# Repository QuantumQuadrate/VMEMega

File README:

VMEMega is a modified ardunino mega board designed to fit into the VME system designed for Saffman lab.
It has 3 communication interfaces (USB/Serial, Ethernet, I2C over backplane) and is designed to host normal mega compatible arduino shields.

Matthew Ebert
Atom Trainers (Walker Lab) and Saffman Lab

Licenced uner the Arduino Creative Commons Share-Alike licence.

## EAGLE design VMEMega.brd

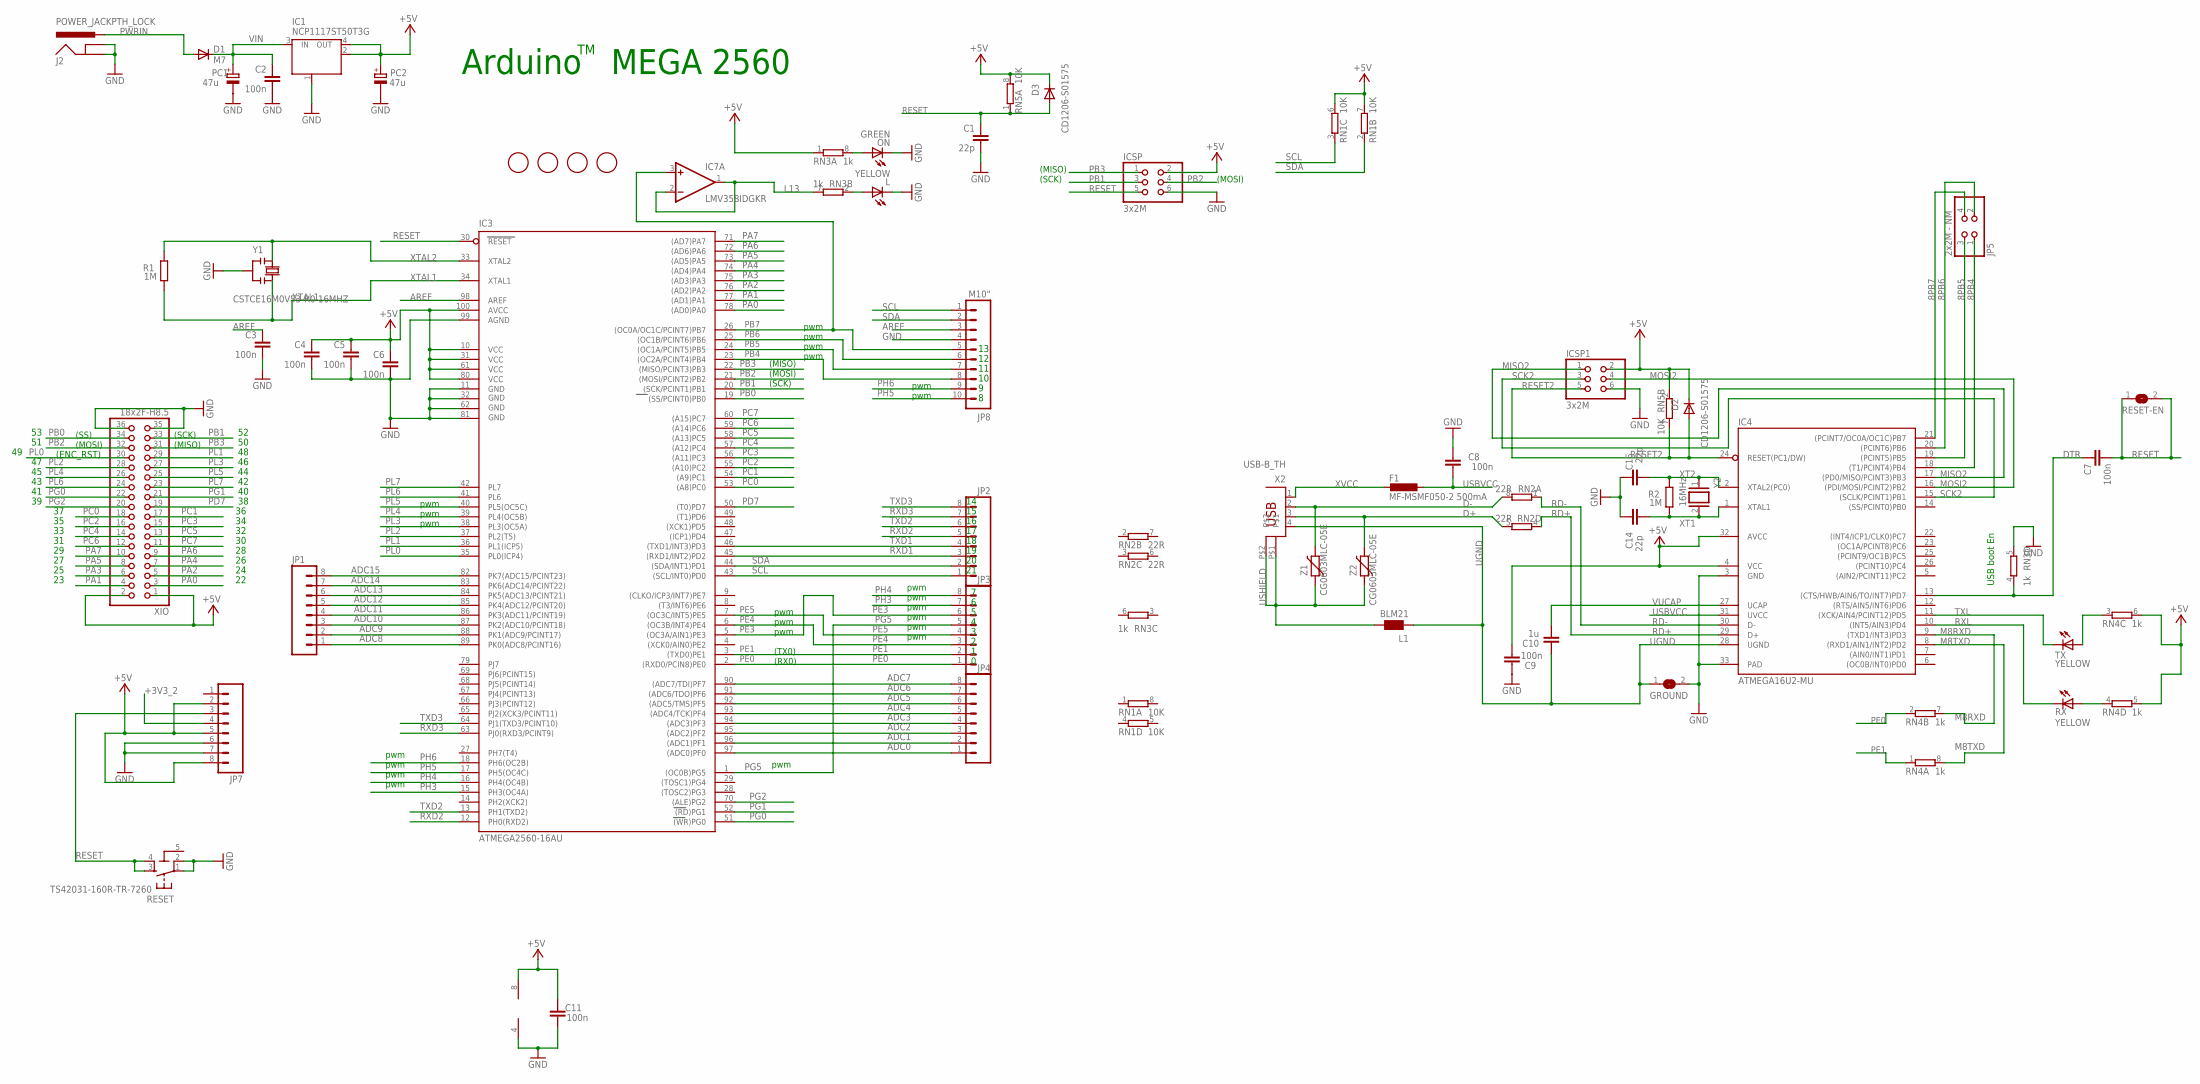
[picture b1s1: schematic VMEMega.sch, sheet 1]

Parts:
C1, C14, C15: 22p; C0603-ROUND
C2, C3, C4, C5, C6, C7, C8, C9, C11: 100n; C0603-ROUND
C10: 1u; C0603-ROUND
D1: M7; SMB
D2, D3: CD1206-S01575; MINIMELF
F1: MF-MSMF050-2 500mA; L1812
FD1, FD2, FD3, FD4: FIDUCIALMOUNT; FIDUCIA-MOUNT
GROUND: SJ
IC1: NCP1117ST50T3G; SOT223
IC3: ATMEGA2560-16AU; TQFP100
IC4: ATMEGA16U2-MU; MLF32
IC7: LMV358IDGKR; MSOP08
ICSP, ICSP1: 3x2M; 2X03
J2: POWER_JACKPTH_LOCK; POWER_JACK_PTH_LOCK
JP1, JP2, JP3, JP4, JP7: M081X08; 1X08
JP5: 2x2M - NM; 2X02
JP8: M10"; 1X10
L: YELLOW; CHIP-LED0805
L1: BLM21; 0805
ON: GREEN; CHIP-LED0805
PC1, PC2: 47u; PANASONIC_D
R1, R2: 1M; R0603-ROUND
RESET: TS42031-160R-TR-7260; TS42
RESET-EN: SJ
RN1, RN5: 10K; CAT16
RN2: 22R; CAY16
RN3, RN4: 1k; CAY16
RX: YELLOW; CHIP-LED0805
TX: YELLOW; CHIP-LED0805
X2: USB-B_TH; PN61729
XIO: 18x2F-H8.5; 2X18
Y1: CSTCE16M0V53-R0 16MHZ; RESONATOR
Y2: 16MHz; QS
Z1, Z2: CG0603MLC-05E; CT/CN0603

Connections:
5-GND: RESET.5 (5-GND)
8PB4: IC4.18 ((T1/PCINT4)PB4), JP5.1
8PB5: IC4.19 ((PCINT5)PB5), JP5.3
8PB6: IC4.20 ((PCINT6)PB6), JP5.2
8PB7: IC4.21 ((PCINT7/OC0A/OC1C)PB7), JP5.4
+3V3_2: JP7.4; also elsewhere on the board
+5V: C4.1, C5.1, C6.1, C9.1, C11.2, D2.C, D3.C, IC1.2 (OUT), IC1.4 (OUT), IC3.10 (VCC), IC3.31 (VCC1), IC3.61 (VCC2), IC3.80 (VCC3), IC3.100 (AVCC), IC4.4 (VCC), IC4.32 (AVCC), IC7.8 (V+), ICSP.2, ICSP1.2, JP7.2, JP7.5, JP7.8, PC2.+, RN1.6 (2), RN1.7 (2), RN3.1, RN4.5 (2), RN4.6 (2), RN5.2 (1), RN5.8 (2), XIO.1, XIO.2; also elsewhere on the board
ADC0: IC3.97 ((ADC0)PF0), JP4.1
ADC1: IC3.96 ((ADC1)PF1), JP4.2
ADC2: IC3.95 ((ADC2)PF2), JP4.3
ADC3: IC3.94 ((ADC3)PF3), JP4.4
ADC4: IC3.93 ((ADC4/TCK)PF4), JP4.5
ADC5: IC3.92 ((ADC5/TMS)PF5), JP4.6
ADC6: IC3.91 ((ADC6/TDO)PF6), JP4.7
ADC7: IC3.90 ((ADC7/TDI)PF7), JP4.8
ADC8: IC3.89 (PK0(ADC8/PCINT16)), JP1.1
ADC9: IC3.88 (PK1(ADC9/PCINT17)), JP1.2
ADC10: IC3.87 (PK2(ADC10/PCINT18)), JP1.3
ADC11: IC3.86 (PK3(ADC11/PCINT19)), JP1.4
ADC12: IC3.85 (PK4(ADC12/PCINT20)), JP1.5
ADC13: IC3.84 (PK5(ADC13/PCINT21)), JP1.6
ADC14: IC3.83 (PK6(ADC14/PCINT22)), JP1.7
ADC15: IC3.82 (PK7(ADC15/PCINT23)), JP1.8
AREF: C3.1, IC3.98 (AREF), JP8.3; also elsewhere on the board
D+: RN2.5 (2), X2.3, Z2.2
D-: RN2.8 (2), X2.2, Z1.2
DTR: C7.1, IC4.13 ((CTS/HWB/AIN6/TO/INT7)PD7), RN3.4 (1)
GND: C1.2, C2.2, C3.2, C4.2, C5.2, C6.2, C8.2, C9.2, C11.1, C14.2, C15.2, GROUND.2, IC1.1 (GND/ADJ), IC3.11 (GND), IC3.32 (GND1), IC3.62 (GND2), IC3.81 (GND3), IC3.99 (AGND), IC4.3 (GND), IC4.33 (PAD), IC7.4 (V-), ICSP.6, ICSP1.6, J2.GND, J2.GNDBREAK, JP7.6, JP7.7, JP8.4, L.C, ON.C, PC1.-, PC2.-, RESET.1, RESET.2, RN3.5 (2), XIO.35, XIO.36, Y1.2; also elsewhere on the board
L13: IC7.1 (OUT), IC7.2 (-IN), RN3.7 (2)
M8RXD: IC4.9 ((TXD1/INT3)PD3), RN4.7 (2)
M8TXD: IC4.8 ((RXD1/AIN1/INT2)PD2), RN4.8 (2)
MISO2: IC4.17 ((PD0/MISO/PCINT3)PB3), ICSP1.1
MOSI2: IC4.16 ((PDI/MOSI/PCINT2)PB2), ICSP1.4
unnamed: L.A, RN3.2 (1)
unnamed: ON.A, RN3.8 (2)
unnamed: RN4.4 (1), RX.A
unnamed: RN4.3 (1), TX.A
PA0: IC3.78 ((AD0)PA0), XIO.3
PA1: IC3.77 ((AD1)PA1), XIO.4
PA2: IC3.76 ((AD2)PA2), XIO.5
PA3: IC3.75 ((AD3)PA3), XIO.6
PA4: IC3.74 ((AD4)PA4), XIO.7
PA5: IC3.73 ((AD5)PA5), XIO.8
PA6: IC3.72 ((AD6)PA6), XIO.9
PA7: IC3.71 ((AD7)PA7), XIO.10
PB0: IC3.19 ((SS/PCINT0)PB0), XIO.34; also elsewhere on the board
PB1: IC3.20 ((SCK/PCINT1)PB1), ICSP.3, XIO.33; also elsewhere on the board
PB2: IC3.21 ((MOSI/PCINT2)PB2), ICSP.4, XIO.32; also elsewhere on the board
PB3: IC3.22 ((MISO/PCINT3)PB3), ICSP.1, XIO.31; also elsewhere on the board
PB4: IC3.23 ((OC2A/PCINT4)PB4), JP8.8
PB5: IC3.24 ((OC1A/PCINT5)PB5), JP8.7
PB6: IC3.25 ((OC1B/PCINT6)PB6), JP8.6
PB7: IC3.26 ((OC0A/OC1C/PCINT7)PB7), IC7.3 (+IN), JP8.5
PC0: IC3.53 ((A8)PC0), XIO.18
PC1: IC3.54 ((A9)PC1), XIO.17
PC2: IC3.55 ((A10)PC2), XIO.16
PC3: IC3.56 ((A11)PC3), XIO.15
PC4: IC3.57 ((A12)PC4), XIO.14
PC5: IC3.58 ((A13)PC5), XIO.13
PC6: IC3.59 ((A14)PC6), XIO.12
PC7: IC3.60 ((A15)PC7), XIO.11
PD7: IC3.50 ((T0)PD7), XIO.19
PE0: IC3.2 ((RXD0/PCIN8)PE0), JP3.1, RN4.2 (1)
PE1: IC3.3 ((TXD0)PE1), JP3.2, RN4.1
PE3: IC3.5 ((OC3A/AIN1)PE3), JP3.6
PE4: IC3.6 ((OC3B/INT4)PE4), JP3.3
PE5: IC3.7 ((OC3C/INT5)PE5), JP3.4
PG0: IC3.51 ((WR)PG0), XIO.22
PG1: IC3.52 ((RD)PG1), XIO.21
PG2: IC3.70 ((ALE)PG2), XIO.20
PG5: IC3.1 ((OC0B)PG5), JP3.5
PH3: IC3.15 (PH3(OC4A)), JP3.7
PH4: IC3.16 (PH4(OC4B)), JP3.8
PH5: IC3.17 (PH5(OC4C)), JP8.10
PH6: IC3.18 (PH6(OC2B)), JP8.9
PL0: IC3.35 (PL0(ICP4)), XIO.30; also elsewhere on the board
PL1: IC3.36 (PL1(ICP5)), XIO.29
PL2: IC3.37 (PL2(T5)), XIO.28
PL3: IC3.38 (PL3(OC5A)), XIO.27
PL4: IC3.39 (PL4(OC5B)), XIO.26
PL5: IC3.40 (PL5(OC5C)), XIO.25
PL6: IC3.41 (PL6), XIO.24
PL7: IC3.42 (PL7), XIO.23
PWRIN: D1.A, J2.PWR
RD+: IC4.29 (D+), RN2.4 (1)
RD-: IC4.30 (D-), RN2.1
RESET: C1.1, C7.2, D3.A, IC3.30 (RESET), ICSP.5, JP7.3, RESET.3, RESET.4, RESET-EN.1, RESET-EN.2, RN5.1
RESET2: D2.A, IC4.24 (RESET(PC1/DW)), ICSP1.5, RN5.7 (2)
RXD1: IC3.45 ((RXD1/INT2)PD2), JP2.3
RXD2: IC3.12 (PH0(RXD2)), JP2.5
RXD3: IC3.63 (PJ0(RXD3/PCINT9)), JP2.7
RXL: IC4.10 ((INT5/AIN3)PD4), RX.C
SCK2: IC4.15 ((SCLK/PCINT1)PB1), ICSP1.3
SCL: IC3.43 ((SCL/INT0)PD0), JP2.1, JP8.1, RN1.3 (1); also elsewhere on the board
SDA: IC3.44 ((SDA/INT1)PD1), JP2.2, JP8.2, RN1.2 (1); also elsewhere on the board
TXD1: IC3.46 ((TXD1/INT3)PD3), JP2.4
TXD2: IC3.13 (PH1(TXD2)), JP2.6
TXD3: IC3.64 (PJ1(TXD3/PCINT10)), JP2.8
TXL: IC4.11 ((XCK/AIN4/PCINT12)PD5), TX.C
UGND: C10.2, GROUND.1, IC4.28 (UGND), L1.1, X2.4
USBVCC: C8.1, F1.1, IC4.31 (UVCC)
USHIELD: L1.2, X2.P$1, X2.P$2, Z1.1, Z2.1
VIN: C2.1, D1.C, IC1.3 (IN), PC1.+
VUCAP: C10.1, IC4.27 (UCAP)
XT1: C14.1, IC4.1 (XTAL1), R2.1, Y2.2
XT2: C15.1, IC4.2 (XTAL2(PC0)), R2.2, Y2.1
XTAL1: IC3.34 (XTAL1), R1.1, Y1.3
XTAL2: IC3.33 (XTAL2), R1.2, Y1.1
XVCC: F1.2, X2.1

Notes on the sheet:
Arduino MEGA 2560
(SCK)
(MISO)
(MOSI)
pwm
(TX0)
(RX0)
(SS)
USB boot En
(ENC_RST)

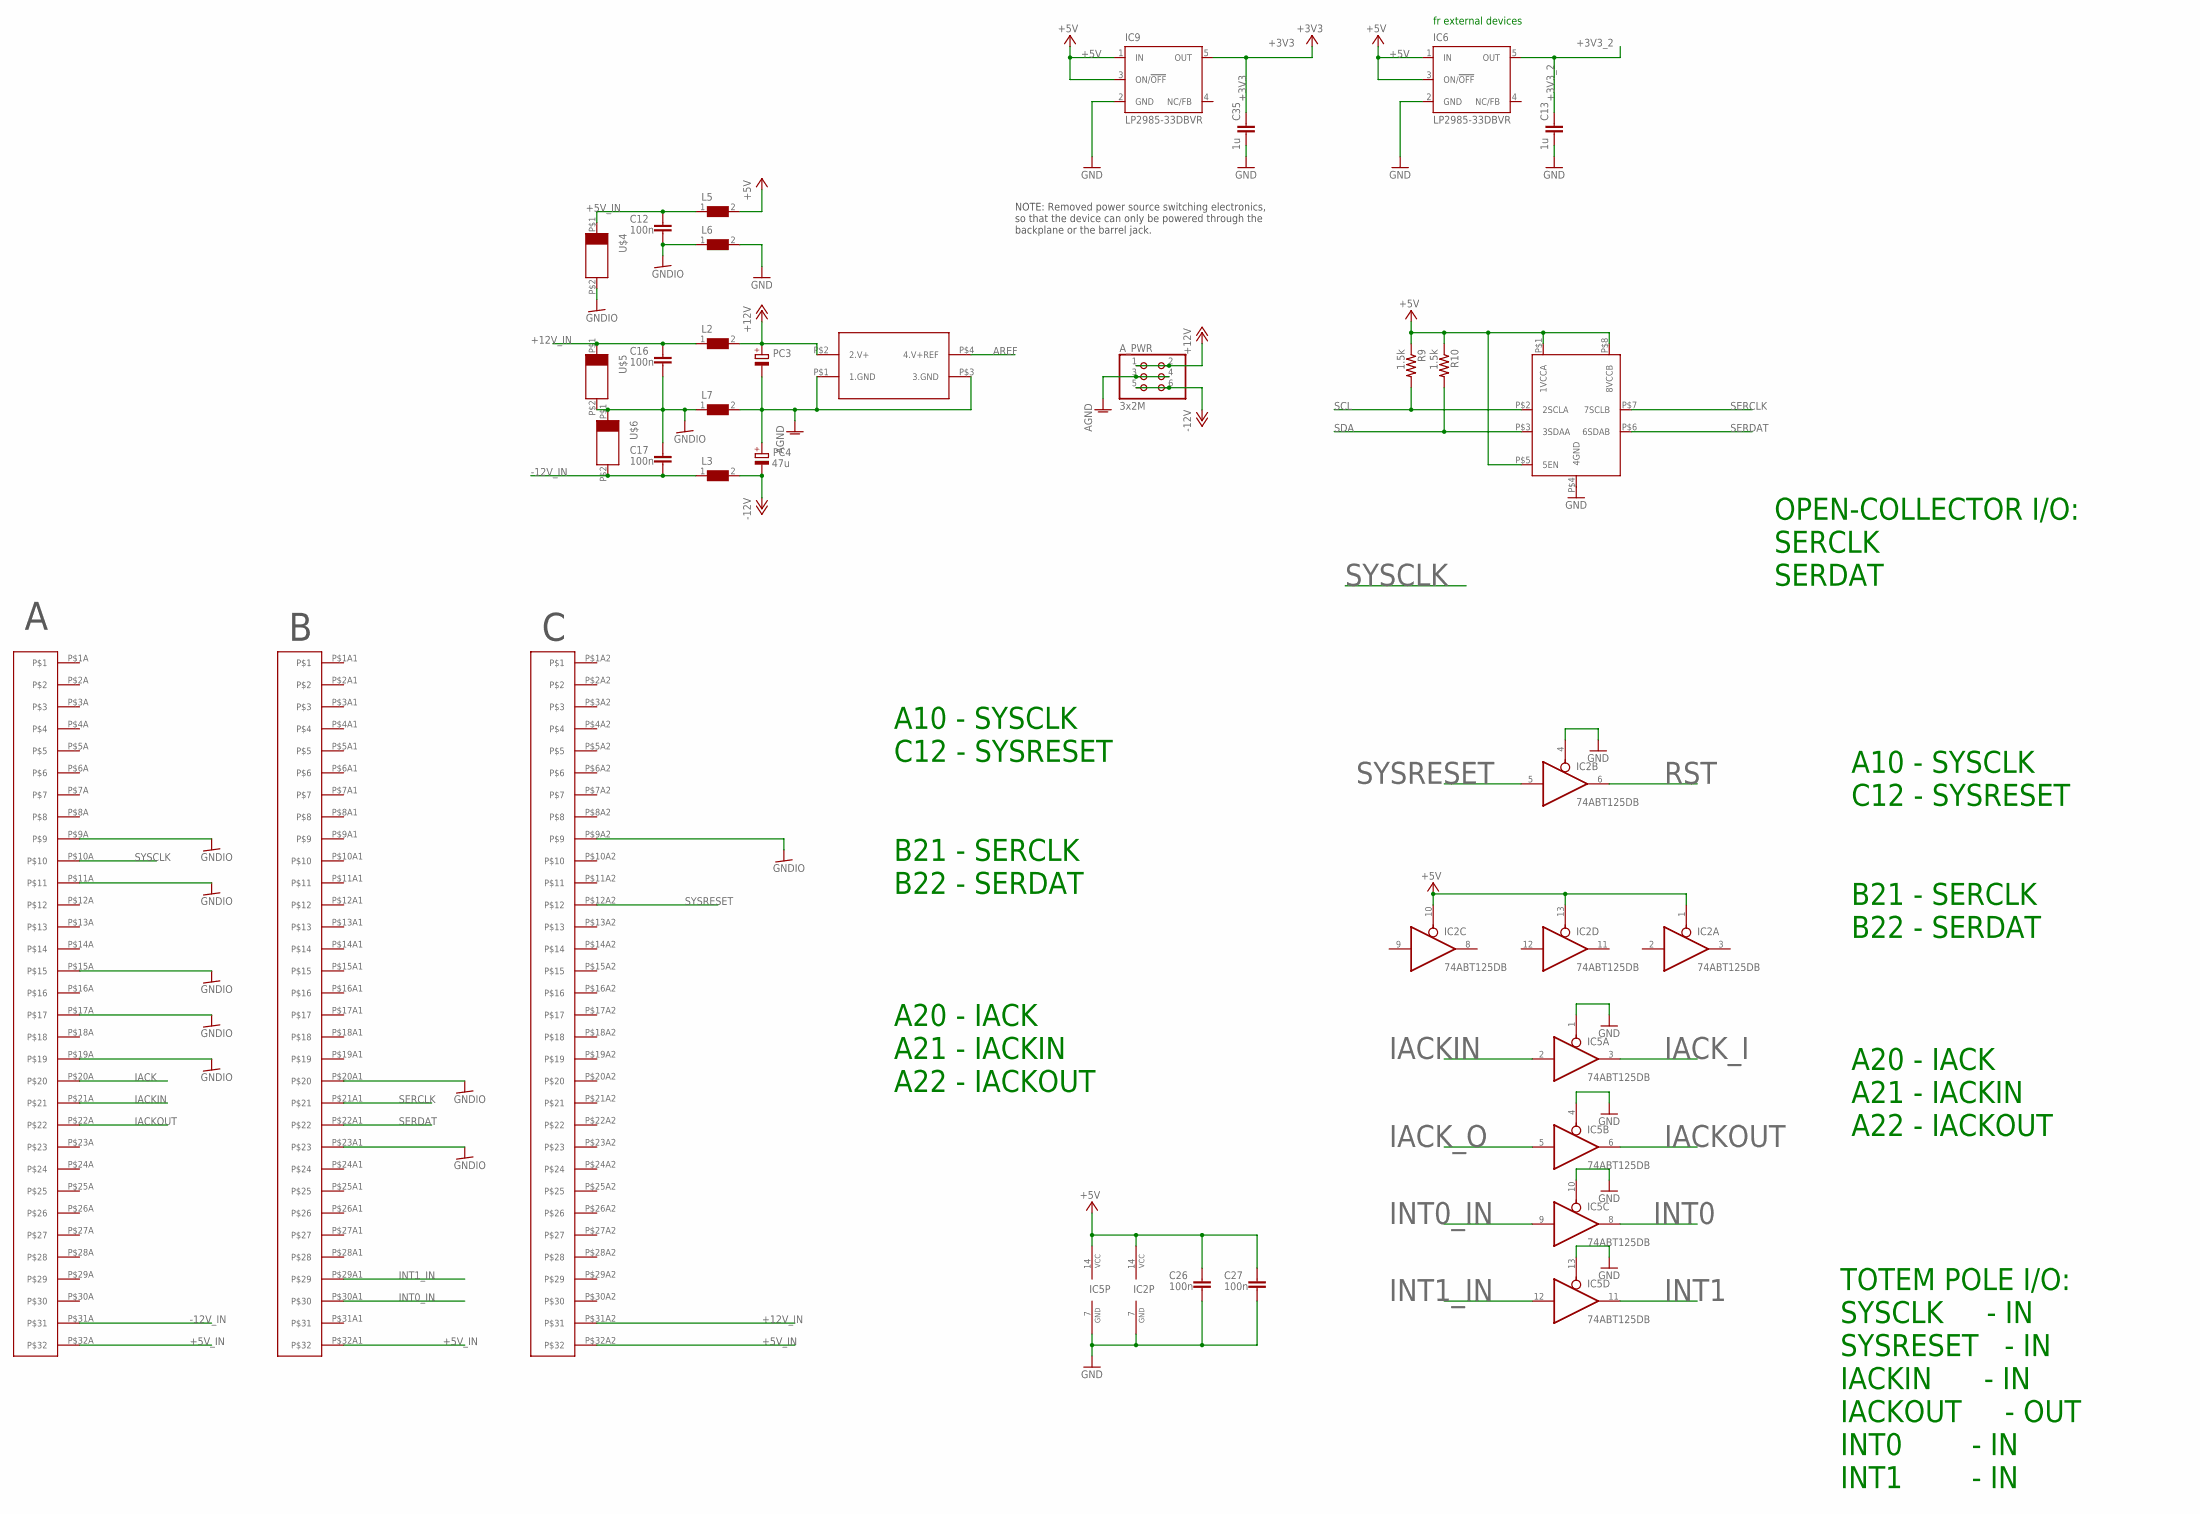
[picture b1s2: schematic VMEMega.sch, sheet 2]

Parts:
A_PWR: 3x2M; 2X03
C12, C16, C17, C26, C27: 100n; C0603-ROUND
C13, C35: 1u; C0603-ROUND
IC2, IC5: 74ABT125DB; SSOP14
IC6, IC9: LP2985-33DBVR; SOT23-DBV
L2, L3, L5, L6, L7: WE-CBF-7427920_0805; 0805
PC3, PC4: 47u; PANASONIC_D
R9, R10: 1.5k; R0603
U$2: TCA9617A; TSSOP-8
U$3: LOWNOISE_VREF_V1B
U$4, U$5, U$6: SMAJ20A; D0-214AC
U$17: DIN_41612_PLUG

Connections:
+3V3: C35.2, IC9.5 (OUT); also elsewhere on the board
+3V3_2: C13.2, IC6.5 (OUT); also elsewhere on the board
+5V: C26.2, C27.2, IC2.1 (OE), IC2.10 (OE), IC2.13 (OE), IC2.14 (VCC), IC5.14 (VCC), IC6.1 (IN), IC6.3 (ON/!OFF), IC9.1 (IN), IC9.3 (ON/!OFF), L5.2, R9.1, R10.1, U$2.P$1 (1VCCA), U$2.P$5 (5EN), U$2.P$8 (8VCCB); also elsewhere on the board
+5V_IN: C12.2, L5.1, U$4.P$1, U$17.P$32A, U$17.P$32A1, U$17.P$32A2
+12V: A_PWR.1, A_PWR.2, L2.2, PC3.+, U$3.P$2 (2.V+)
+12V_IN: C16.2, L2.1, U$5.P$1, U$17.P$31A2
-12V: A_PWR.5, A_PWR.6, L3.2, PC4.-
-12V_IN: C17.1, L3.1, U$6.P$2, U$17.P$31A
AGND: A_PWR.3, A_PWR.4, L7.2, PC3.-, PC4.+, U$3.P$1 (1.GND), U$3.P$3 (3.GND)
AREF: U$3.P$4 (4.V+REF); also elsewhere on the board
GND: C13.1, C26.1, C27.1, C35.1, IC2.4 (OE), IC2.7 (GND), IC5.4 (OE), IC5.7 (GND), IC5.10 (OE), IC5.13 (OE), IC6.2 (GND), IC9.2 (GND), L6.2, U$2.P$4 (4GND); also elsewhere on the board
GNDIO: C12.1, C16.1, C17.2, L6.1, L7.1, U$4.P$2, U$5.P$2, U$6.P$1, U$17.P$9A, U$17.P$9A2, U$17.P$11A, U$17.P$15A, U$17.P$17A, U$17.P$19A, U$17.P$20A1, U$17.P$23A1
IACK: U$17.P$20A
IACKIN: IC5.2 (I), U$17.P$21A
IACKOUT: IC5.6 (O), U$17.P$22A
IACK_I: IC5.3 (O)
IACK_O: IC5.5 (I)
INT0: IC5.8 (O)
INT0_IN: IC5.9 (I), U$17.P$30A1
INT1: IC5.11 (O)
INT1_IN: IC5.12 (I), U$17.P$29A1
RST: IC2.6 (O)
SCL: R9.2, U$2.P$2 (2SCLA); also elsewhere on the board
SDA: R10.2, U$2.P$3 (3SDAA); also elsewhere on the board
SERCLK: U$2.P$7 (7SCLB), U$17.P$21A1
SERDAT: U$2.P$6 (6SDAB), U$17.P$22A1
SYSCLK: U$17.P$10A
SYSRESET: IC2.5 (I), U$17.P$12A2

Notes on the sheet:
A10 - SYSCLK C12 - SYSRESET
B21 - SERCLK B22 - SERDAT
A20 - IACK A21 - IACKIN A22 - IACKOUT
TOTEM POLE I/O: SYSCLK - IN SYSRESET - IN IACKIN - IN IACKOUT - OUT INT0 - IN INT1 - IN
OPEN-COLLECTOR I/O: SERCLK SERDAT
NOTE: Removed power source switching electronics, so that the device can only be powered through the backplane or the barrel jack.
fr external devices

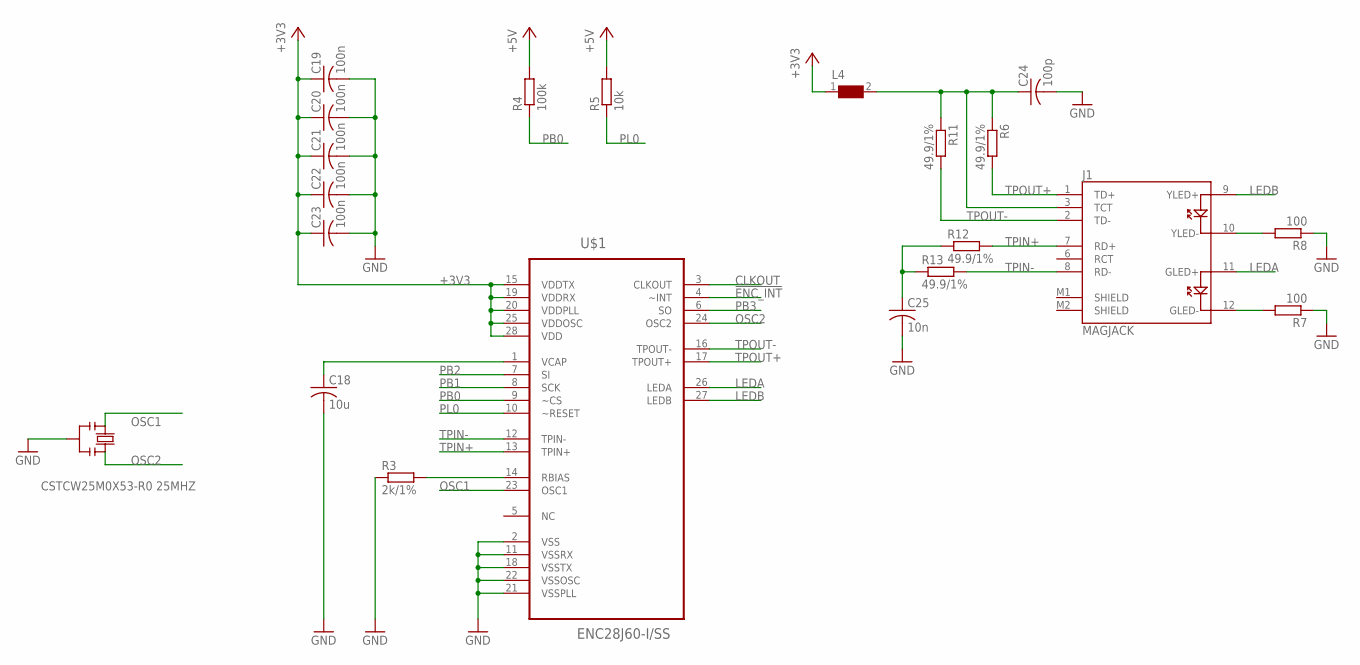
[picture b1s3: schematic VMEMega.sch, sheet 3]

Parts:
C18: 10u; C1206
C19, C20, C21, C22, C23: 100n; C0603
C24: 100p; C0603
C25: 10n; C0603
J1: MAGJACK
L4: WE-CBF-74279206_0805; 0805
R3: 2k/1%; R0603
R4: 100k; R0603
R5: 10k; R0603
R6, R11, R12, R13: 49.9/1%; R0603
R7, R8: 100; R0603
U$1: ENC28J60-I/SS; SOP65P780X200-28N
Y3: CSTCW25M0X53-R0 25MHZ; RESONATOR

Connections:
!ENC_INT: U$1.4 (~INT)
+3V3: C19.1, C20.1, C21.1, C22.1, C23.1, L4.1, U$1.15 (VDDTX), U$1.19 (VDDRX), U$1.20 (VDDPLL), U$1.25 (VDDOSC), U$1.28 (VDD); also elsewhere on the board
+5V: R4.2, R5.2; also elsewhere on the board
CLKOUT: U$1.3 (CLKOUT)
GND: C18.2, C19.2, C20.2, C21.2, C22.2, C23.2, C24.2, C25.2, R3.1, R7.1, R8.1, U$1.2 (VSS), U$1.11 (VSSRX), U$1.18 (VSSTX), U$1.21 (VSSPLL), U$1.22 (VSSOSC), Y3.2; also elsewhere on the board
LEDA: J1.11 (GLED+), U$1.26 (LEDA)
LEDB: J1.9 (YLED+), U$1.27 (LEDB)
unnamed: J1.12 (GLED-), R7.2
unnamed: J1.10 (YLED-), R8.2
unnamed: C25.1, R12.1, R13.1
unnamed: C24.1, J1.3 (TCT), L4.2, R6.1, R11.1
unnamed: R3.2, U$1.14 (RBIAS)
unnamed: C18.1, U$1.1 (VCAP)
OSC1: U$1.23 (OSC1), Y3.1
OSC2: U$1.24 (OSC2), Y3.3
PB0: R4.1, U$1.9 (~CS); also elsewhere on the board
PB1: U$1.8 (SCK); also elsewhere on the board
PB2: U$1.7 (SI); also elsewhere on the board
PB3: U$1.6 (SO); also elsewhere on the board
PL0: R5.1, U$1.10 (~RESET); also elsewhere on the board
TPIN+: J1.7 (RD+), R12.2, U$1.13 (TPIN+)
TPIN-: J1.8 (RD-), R13.2, U$1.12 (TPIN-)
TPOUT+: J1.1 (TD+), R6.2, U$1.17 (TPOUT+)
TPOUT-: J1.2 (TD-), R11.2, U$1.16 (TPOUT-)

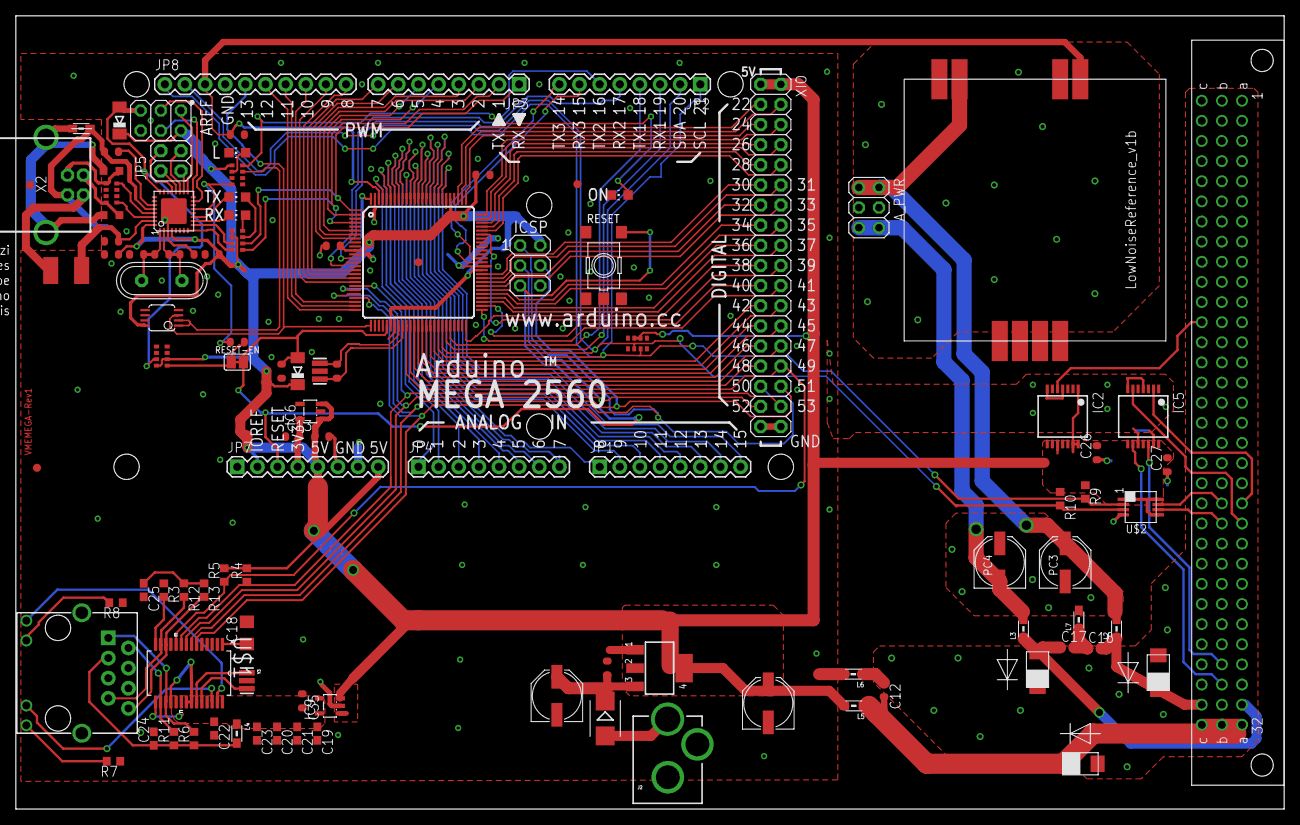
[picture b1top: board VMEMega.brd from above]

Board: 2 copper layers, 160.0 x 100.1 mm, 106 parts (1 on the bottom side), 137 nets.

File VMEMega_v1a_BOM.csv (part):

"Part";"Value";"Device";"Package";"Description";"MF";"MPN";"OC_FARNELL";"OC_NEWARK";"PACKAGE";"PROD_ID";"SUPPLIER";
"A_PWR";"3x2M";"PINHD-2X3";"2X03";"PIN HEADER";"";"";"";"";"";"";"";
"C1";"22p";"C-EU0603-RND";"C0603-ROUND";"CAPACITOR, European symbol";"";"";"";"";"";"";"";
"C2";"100n";"C-EU0603-RND";"C0603-ROUND";"CAPACITOR, European symbol";"";"";"";"";"";"";"";
"C3";"100n";"C-EU0603-RND";"C0603-ROUND";"CAPACITOR, European symbol";"";"";"";"";"";"";"";
"C4";"100n";"C-EU0603-RND";"C0603-ROUND";"CAPACITOR, European symbol";"";"";"";"";"";"";"";
"C5";"100n";"C-EU0603-RND";"C0603-ROUND";"CAPACITOR, European symbol";"";"";"";"";"";"";"";
"C6";"100n";"C-EU0603-RND";"C0603-ROUND";"CAPACITOR, European symbol";"";"";"";"";"";"";"";
"C7";"100n";"C-EU0603-RND";"C0603-ROUND";"CAPACITOR, European symbol";"";"";"";"";"";"";"";
"C8";"100n";"C-EU0603-RND";"C0603-ROUND";"CAPACITOR, European symbol";"";"";"";"";"";"";"";
"C9";"100n";"C-EU0603-RND";"C0603-ROUND";"CAPACITOR, European symbol";"";"";"";"";"";"";"";
"C10";"1u";"C-EU0603-RND";"C0603-ROUND";"CAPACITOR, European symbol";"";"";"";"";"";"";"";
"C11";"100n";"C-EU0603-RND";"C0603-ROUND";"CAPACITOR, European symbol";"";"";"";"";"";"";"";
"C12";"100n";"C-EU0603-RND";"C0603-ROUND";"CAPACITOR, European symbol";"";"";"";"";"";"";"";
"C13";"1u";"C-EU0603-RND";"C0603-ROUND";"CAPACITOR, European symbol";"";"";"";"";"";"";"";
"C14";"22p";"C-EU0603-RND";"C0603-ROUND";"CAPACITOR, European symbol";"";"";"";"";"";"";"";
"C15";"22p";"C-EU0603-RND";"C0603-ROUND";"CAPACITOR, European symbol";"";"";"";"";"";"";"";
"C16";"100n";"C-EU0603-RND";"C0603-ROUND";"CAPACITOR, European symbol";"";"";"";"";"";"";"";
"C17";"100n";"C-EU0603-RND";"C0603-ROUND";"CAPACITOR, European symbol";"";"";"";"";"";"";"";
"C18";"10u";"C-USC1206";"C1206";"CAPACITOR, American symbol";"";"";"";"";"";"";"";
"C19";"100n";"C-USC0603";"C0603";"CAPACITOR, American symbol";"";"";"";"";"";"";"";
"C20";"100n";"C-USC0603";"C0603";"CAPACITOR, American symbol";"";"";"";"";"";"";"";
"C21";"100n";"C-USC0603";"C0603";"CAPACITOR, American symbol";"";"";"";"";"";"";"";
"C22";"100n";"C-USC0603";"C0603";"CAPACITOR, American symbol";"";"";"";"";"";"";"";
"C23";"100n";"C-USC0603";"C0603";"CAPACITOR, American symbol";"";"";"";"";"";"";"";
"C24";"100p";"C-USC0603";"C0603";"CAPACITOR, American symbol";"";"";"";"";"";"";"";
"C25";"10n";"C-USC0603";"C0603";"CAPACITOR, American symbol";"";"";"";"";"";"";"";
"C26";"100n";"C-EU0603-RND";"C0603-ROUND";"CAPACITOR, European symbol";"";"";"";"";"";"";"";
"C27";"100n";"C-EU0603-RND";"C0603-ROUND";"CAPACITOR, European symbol";"";"";"";"";"";"";"";
"C35";"1u";"C-EU0603-RND";"C0603-ROUND";"CAPACITOR, European symbol";"";"";"";"";"";"";"";
"D1";"M7";"DIODE-SMB";"SMB";"DIODE";"";"";"";"";"";"";"";
"D2";"CD1206-S01575";"DIODE-MINIMELF";"MINIMELF";"DIODE";"";"";"";"";"";"";"";
"D3";"CD1206-S01575";"DIODE-MINIMELF";"MINIMELF";"DIODE";"";"";"";"";"";"";"";
"F1";"MF-MSMF050-2 500mA";"L-EUL1812";"L1812";"INDUCTOR, European symbol";"";"";"";"";"";"";"";
"FD1";"FIDUCIALMOUNT";"FIDUCIALMOUNT";"FIDUCIA-MOUNT";"";"";"";"";"";"";"";"";
"FD2";"FIDUCIALMOUNT";"FIDUCIALMOUNT";"FIDUCIA-MOUNT";"";"";"";"";"";"";"";"";
"FD3";"FIDUCIALMOUNT";"FIDUCIALMOUNT";"FIDUCIA-MOUNT";"";"";"";"";"";"";"";"";
"FD4";"FIDUCIALMOUNT";"FIDUCIALMOUNT";"FIDUCIA-MOUNT";"";"";"";"";"";"";"";"";
"GROUND";"";"SJ";"SJ";"SMD solder JUMPER";"";"";"";"";"";"";"";
"IC1";"NCP1117ST50T3G";"MC33269ST-3.3T3";"SOT223";"Adjustable Output Low Dropout Voltage Regulator 800 mA";"";"";"";"";"";"";"";
"IC2";"74ABT125DB";"74ABT125DB";"SSOP14";"Quad bus BUFFER, 3-state";"";"";"";"";"";"";"";
"IC3";"ATMEGA2560-16AU";"ATMEGA25602560-16AU";"TQFP100";"MICROCONTROLLER";"";"";"";"";"";"";"";
"IC4";"ATMEGA16U2-MU";"ATMEGA16U2-MU";"MLF32";"";"";"";"";"";"";"";"";
"IC5";"74ABT125DB";"74ABT125DB";"SSOP14";"Quad bus BUFFER, 3-state";"";"";"";"";"";"";"";
"IC6";"LP2985-33DBVR";"LP2985-XXDBVR33";"SOT23-DBV";"ULTRALOW-POWER 50-mA LOW-DROPOUT LINEAR REGULATORS";"";"";"";"";"";"";"";
"IC7";"LMV358IDGKR";"LMV358MMX";"MSOP08";"Dual General Purpose, Low Voltage, Rail-to-Rail Output Operational Amplifiers";"";"";"";"";"";"";"";
"IC9";"LP2985-33DBVR";"LP2985-XXDBVR33";"SOT23-DBV";"ULTRALOW-POWER 50-mA LOW-DROPOUT LINEAR REGULATORS";"";"";"";"";"";"";"";
"ICSP";"3x2M";"PINHD-2X3";"2X03";"PIN HEADER";"";"";"";"";"";"";"";
"ICSP1";"3x2M";"PINHD-2X3";"2X03";"PIN HEADER";"";"";"";"";"";"";"";
"J1";"MAGJACK";"MAGJACK";"MAGJACK";"RJ-45 with LEDs";"";"";"";"";"";"";"";
"J2";"POWER_JACKPTH_LOCK";"POWER_JACKPTH_LOCK";"POWER_JACK_PTH_LOCK";"Power Jack";"";"";"";"";"";"PRT-00119";"";
"JP1";"";"M081X08";"1X08";"Header 8";"";"";"";"";"";"";"";
"JP2";"";"M081X08";"1X08";"Header 8";"";"";"";"";"";"";"";
"JP3";"";"M081X08";"1X08";"Header 8";"";"";"";"";"";"";"";
"JP4";"";"M081X08";"1X08";"Header 8";"";"";"";"";"";"";"";
"JP5";"2x2M - NM";"PINHD-2X2";"2X02";"PIN HEADER";"";"";"";"";"";"";"";
"JP7";"";"M081X08";"1X08";"Header 8";"";"";"";"";"";"";"";
"JP8";"M10"";"M10"";"1X10";"Header 10";"";"";"";"";"";"";"";
"L";"YELLOW";"LEDCHIP-LED0805";"CHIP-LED0805";"LED";"";"";"";"";"";"";"";
"L1";"BLM21";"WE-CBF_0805";"0805";"SMD EMI Suppression Ferrite Beads";"";"";"";"";"";"";"";
"L2";"";"WE-CBF-7427920_0805";"0805";"SMD EMI Suppression Ferrite Beads WE-CBF";"";"7427920";"1635707";"08P2358";"IND-0805";"";"Wuerth Elektronik";
"L3";"";"WE-CBF-7427920_0805";"0805";"SMD EMI Suppression Ferrite Beads WE-CBF";"";"7427920";"1635707";"08P2358";"IND-0805";"";"Wuerth Elektronik";
"L4";"";"WE-CBF-74279206_0805";"0805";"SMD EMI Suppression Ferrite Beads WE-CBF";"";"74279206";"1635729";"08P2376";"IND-0805";"";"Wuerth Elektronik";
"L5";"";"WE-CBF-7427920_0805";"0805";"SMD EMI Suppression Ferrite Beads WE-CBF";"";"7427920";"1635707";"08P2358";"IND-0805";"";"Wuerth Elektronik";
"L6";"";"WE-CBF-7427920_0805";"0805";"SMD EMI Suppression Ferrite Beads WE-CBF";"";"7427920";"1635707";"08P2358";"IND-0805";"";"Wuerth Elektronik";
"L7";"";"WE-CBF-7427920_0805";"0805";"SMD EMI Suppression Ferrite Beads WE-CBF";"";"7427920";"1635707";"08P2358";"IND-0805";"";"Wuerth Elektronik";
"ON";"GREEN";"LEDCHIP-LED0805";"CHIP-LED0805";"LED";"";"";"";"";"";"";"";
"PC1";"47u";"CPOL-EUD";"PANASONIC_D";"POLARIZED CAPACITOR, European symbol";"";"";"";"";"";"";"";
"PC2";"47u";"CPOL-EUD";"PANASONIC_D";"POLARIZED CAPACITOR, European symbol";"";"";"";"";"";"";"";
"PC3";"47u";"CPOL-EUD";"PANASONIC_D";"POLARIZED CAPACITOR, European symbol";"";"";"";"";"";"";"";
"PC4";"47u";"CPOL-EUD";"PANASONIC_D";"POLARIZED CAPACITOR, European symbol";"";"";"";"";"";"";"";
"R1";"1M";"R-EU_R0603";"R0603-ROUND";"RESISTOR, European symbol";"";"";"";"";"";"";"";
"R2";"1M";"R-EU_R0603";"R0603-ROUND";"RESISTOR, European symbol";"";"";"";"";"";"";"";
"R3";"2k/1%";"R-EU_R0603";"R0603";"RESISTOR, European symbol";"";"";"";"";"";"";"";
"R4";"100k";"R-EU_R0603";"R0603";"RESISTOR, European symbol";"";"";"";"";"";"";"";
"R5";"10k";"R-EU_R0603";"R0603";"RESISTOR, European symbol";"";"";"";"";"";"";"";
"R6";"49.9/1%";"R-EU_R0603";"R0603";"RESISTOR, European symbol";"";"";"";"";"";"";"";
"R7";"100";"R-EU_R0603";"R0603";"RESISTOR, European symbol";"";"";"";"";"";"";"";
"R8";"100";"R-EU_R0603";"R0603";"RESISTOR, European symbol";"";"";"";"";"";"";"";
"R9";"1.5k";"R-US_R0603";"R0603";"RESISTOR, American symbol";"";"";"";"";"";"";"";
"R10";"1.5k";"R-US_R0603";"R0603";"RESISTOR, American symbol";"";"";"";"";"";"";"";
"R11";"49.9/1%";"R-EU_R0603";"R0603";"RESISTOR, European symbol";"";"";"";"";"";"";"";
"R12";"49.9/1%";"R-EU_R0603";"R0603";"RESISTOR, European symbol";"";"";"";"";"";"";"";
"R13";"49.9/1%";"R-EU_R0603";"R0603";"RESISTOR, European symbol";"";"";"";"";"";"";"";
"RESET";"TS42031-160R-TR-7260";"TS42";"TS42";"TS42";"";"";"";"";"";"";"";
"RESET-EN";"";"SJ";"SJ";"SMD solder JUMPER";"";"";"";"";"";"";"";
"RN1";"10K";"4R-NCAT16";"CAT16";"Array Chip Resistor";"";"";"unknown";"unknown";"";"";"";
"RN2";"22R";"4R-NCAY16";"CAY16";"Array Chip Resistor";"";"";"unknown";"unknown";"";"";"";
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
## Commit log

2016-01-23 Verison 1 Rev A, sent to pcb house
2017-04-20 spelling correction

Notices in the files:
parts and their libraries:
SparkFun-Connectors: Licensing: Creative Commons ShareAlike 4.0 International - https://creativecommons.org/licenses/by-sa/4.0
